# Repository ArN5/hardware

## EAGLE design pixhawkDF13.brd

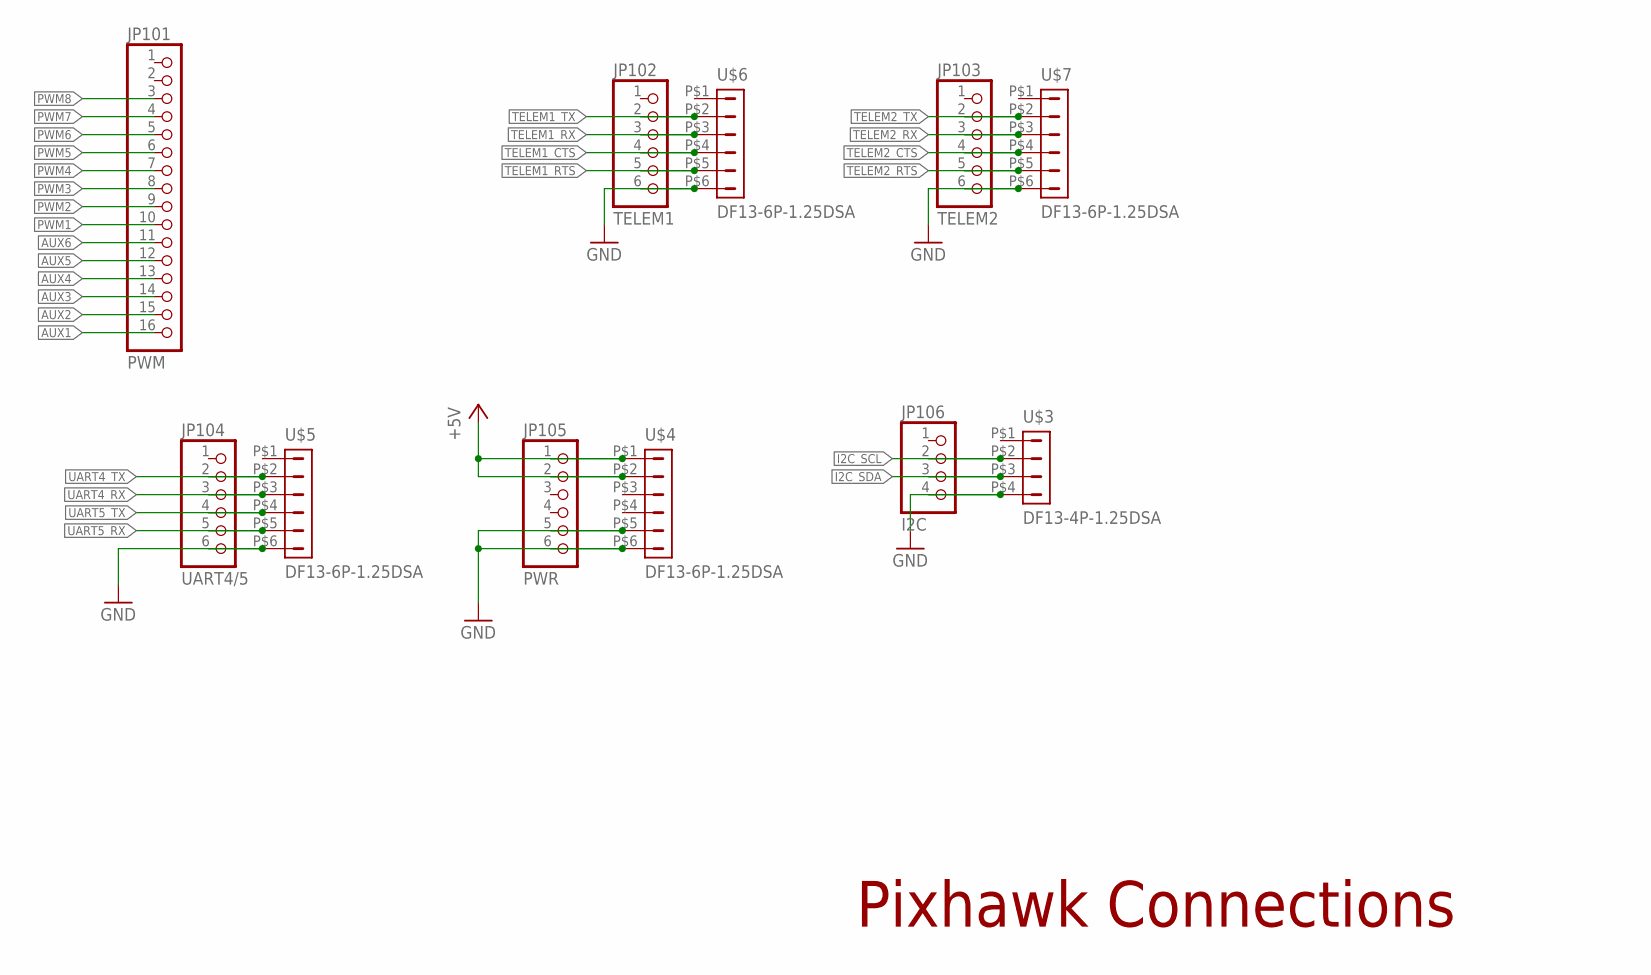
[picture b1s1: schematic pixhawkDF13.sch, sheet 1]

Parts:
JP101: PWM; 1X16
JP102: TELEM1; 1X06
JP103: TELEM2; 1X06
JP104: UART4/5; 1X06
JP105: PWR; 1X06
JP106: I2C; 1X04
U$3: DF13-4P-1.25DSA
U$4, U$5, U$6, U$7: DF13-6P-1.25DSA

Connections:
+5V: JP105.1, JP105.2, U$4.P$1 (1), U$4.P$2 (2); also elsewhere on the board
AUX1: JP101.16; also elsewhere on the board
AUX2: JP101.15; also elsewhere on the board
AUX3: JP101.14; also elsewhere on the board
AUX4: JP101.13; also elsewhere on the board
AUX5: JP101.12; also elsewhere on the board
AUX6: JP101.11; also elsewhere on the board
GND: JP102.6, JP103.6, JP104.6, JP105.5, JP105.6, JP106.4, U$3.P$4 (4), U$4.P$5 (5), U$4.P$6 (6), U$5.P$6 (6), U$6.P$6 (6), U$7.P$6 (6); also elsewhere on the board
I2C_SCL: JP106.2, U$3.P$2 (2); also elsewhere on the board
I2C_SDA: JP106.3, U$3.P$3 (3); also elsewhere on the board
PWM1: JP101.10; also elsewhere on the board
PWM2: JP101.9; also elsewhere on the board
PWM3: JP101.8; also elsewhere on the board
PWM4: JP101.7; also elsewhere on the board
PWM5: JP101.6; also elsewhere on the board
PWM6: JP101.5; also elsewhere on the board
PWM7: JP101.4; also elsewhere on the board
PWM8: JP101.3; also elsewhere on the board
TELEM1_CTS: JP102.4, U$6.P$4 (4)
TELEM1_RTS: JP102.5, U$6.P$5 (5)
TELEM1_RX: JP102.3, U$6.P$3 (3); also elsewhere on the board
TELEM1_TX: JP102.2, U$6.P$2 (2); also elsewhere on the board
TELEM2_CTS: JP103.4, U$7.P$4 (4)
TELEM2_RTS: JP103.5, U$7.P$5 (5)
TELEM2_RX: JP103.3, U$7.P$3 (3); also elsewhere on the board
TELEM2_TX: JP103.2, U$7.P$2 (2); also elsewhere on the board
UART4_RX: JP104.3, U$5.P$3 (3); also elsewhere on the board
UART4_TX: JP104.2, U$5.P$2 (2); also elsewhere on the board
UART5_RX: JP104.5, U$5.P$5 (5); also elsewhere on the board
UART5_TX: JP104.4, U$5.P$4 (4); also elsewhere on the board

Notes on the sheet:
Pixhawk Connections

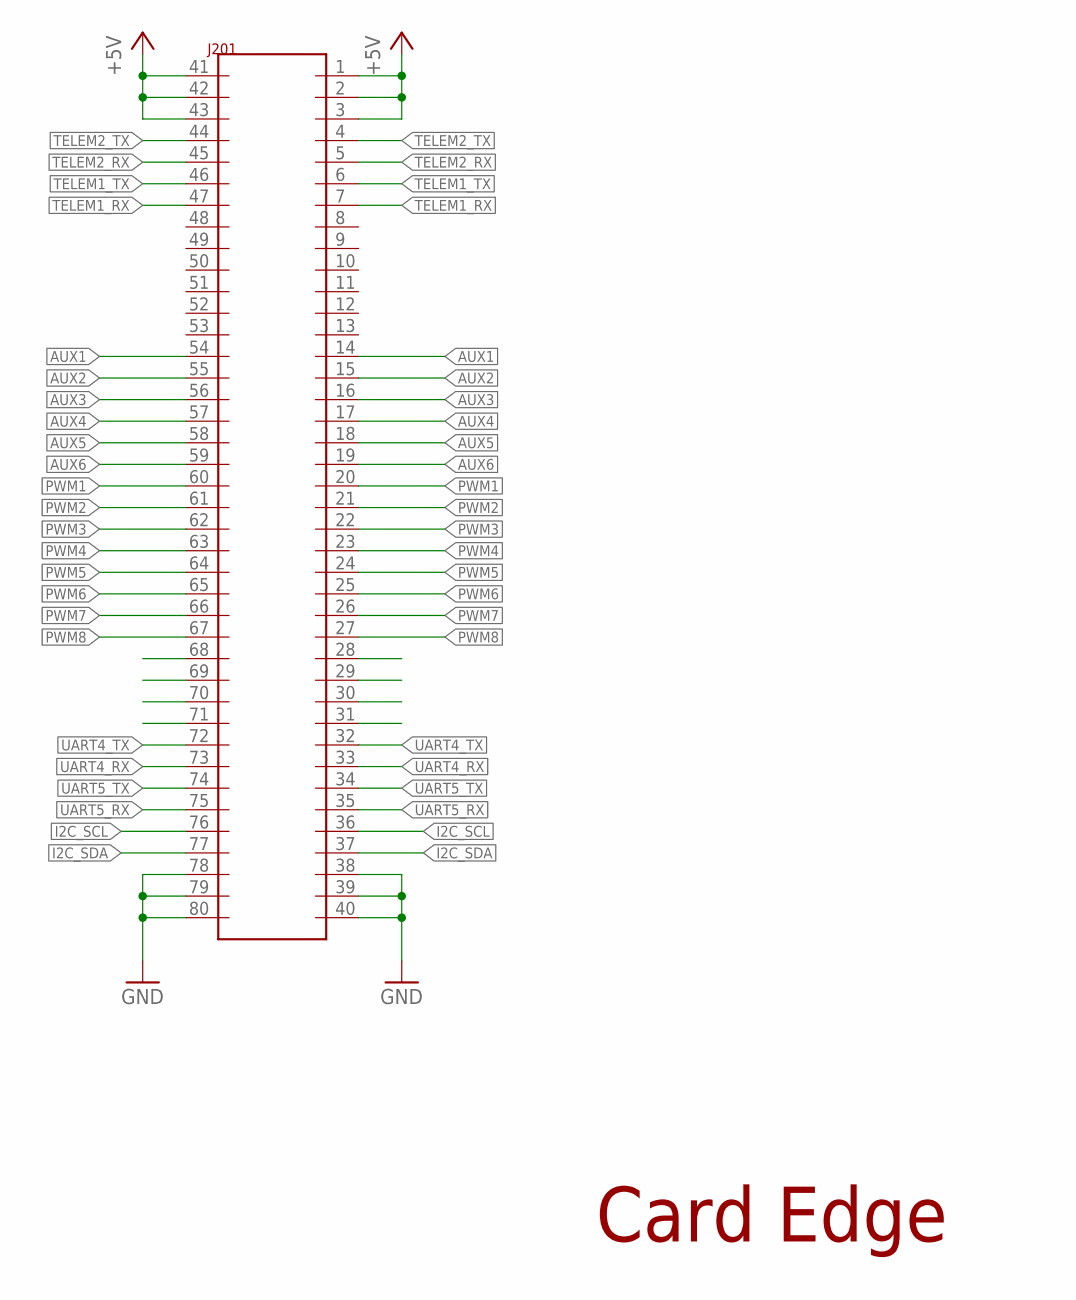
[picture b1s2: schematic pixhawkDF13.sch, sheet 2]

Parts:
J201: 80-PIN-CARD-EDGE

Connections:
+5V: J201.1, J201.2, J201.3, J201.41, J201.42, J201.43; also elsewhere on the board
AUX1: J201.14, J201.54; also elsewhere on the board
AUX2: J201.15, J201.55; also elsewhere on the board
AUX3: J201.16, J201.56; also elsewhere on the board
AUX4: J201.17, J201.57; also elsewhere on the board
AUX5: J201.18, J201.58; also elsewhere on the board
AUX6: J201.19, J201.59; also elsewhere on the board
CAN_H: J201.30, J201.70
CAN_L: J201.31, J201.71
GND: J201.38, J201.39, J201.40, J201.78, J201.79, J201.80; also elsewhere on the board
I2C_SCL: J201.36, J201.76; also elsewhere on the board
I2C_SDA: J201.37, J201.77; also elsewhere on the board
PWM1: J201.20, J201.60; also elsewhere on the board
PWM2: J201.21, J201.61; also elsewhere on the board
PWM3: J201.22, J201.62; also elsewhere on the board
PWM4: J201.23, J201.63; also elsewhere on the board
PWM5: J201.24, J201.64; also elsewhere on the board
PWM6: J201.25, J201.65; also elsewhere on the board
PWM7: J201.26, J201.66; also elsewhere on the board
PWM8: J201.27, J201.67; also elsewhere on the board
TELEM1_RX: J201.7, J201.47; also elsewhere on the board
TELEM1_TX: J201.6, J201.46; also elsewhere on the board
TELEM2_RX: J201.5, J201.45; also elsewhere on the board
TELEM2_TX: J201.4, J201.44; also elsewhere on the board
UART4_RX: J201.33, J201.73; also elsewhere on the board
UART4_TX: J201.32, J201.72; also elsewhere on the board
UART5_RX: J201.35, J201.75; also elsewhere on the board
UART5_TX: J201.34, J201.74; also elsewhere on the board

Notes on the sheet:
Card Edge

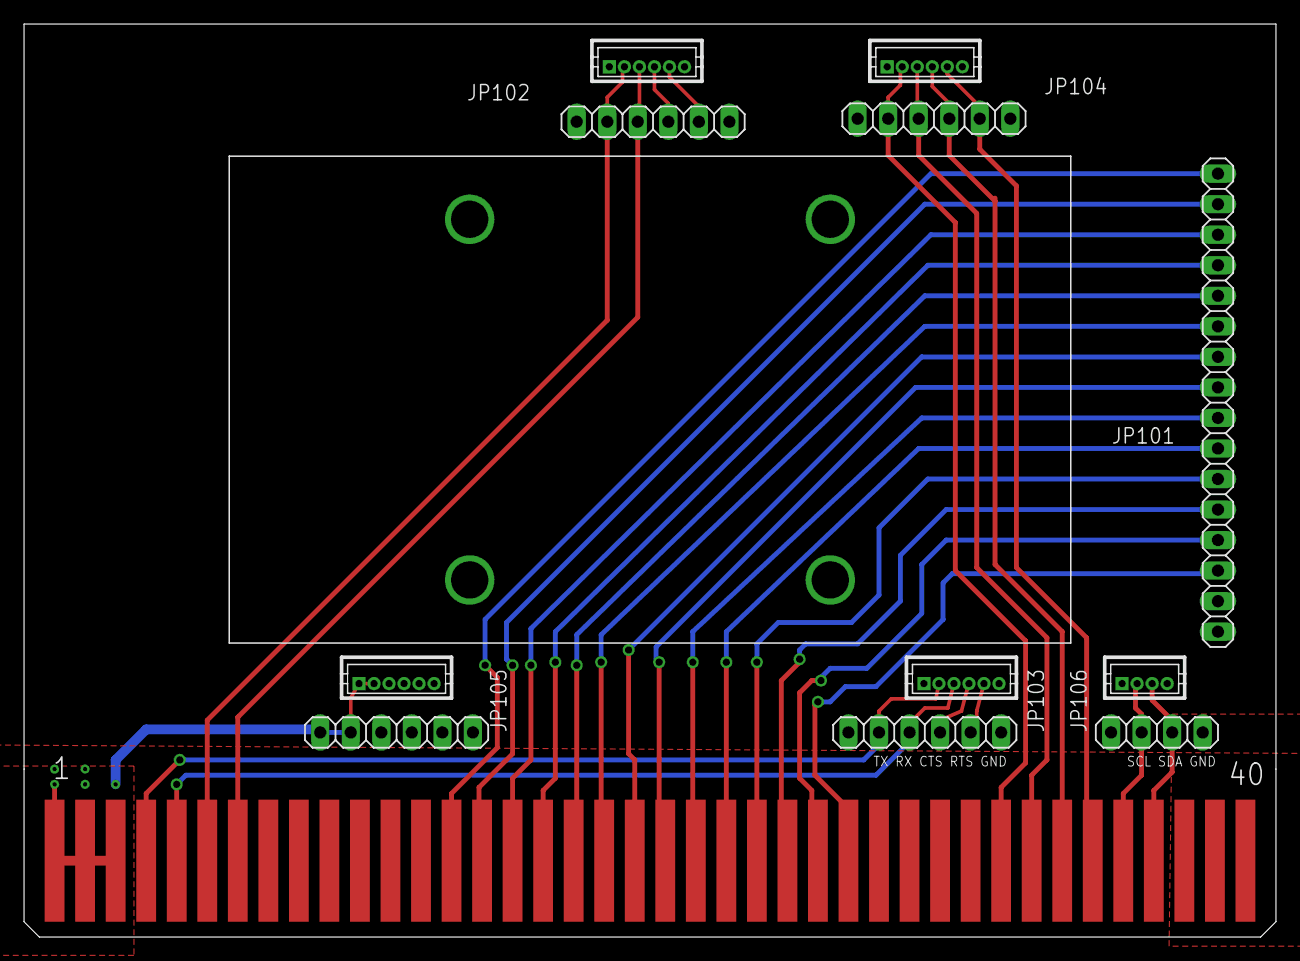
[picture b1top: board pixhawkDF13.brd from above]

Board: 2 copper layers, 104.1 x 75.9 mm, 14 parts (1 on the bottom side), 32 nets.

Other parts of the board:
U$1: PIXHAWK_MOUNTING_HOLES
U$2: ILLINOISAUV

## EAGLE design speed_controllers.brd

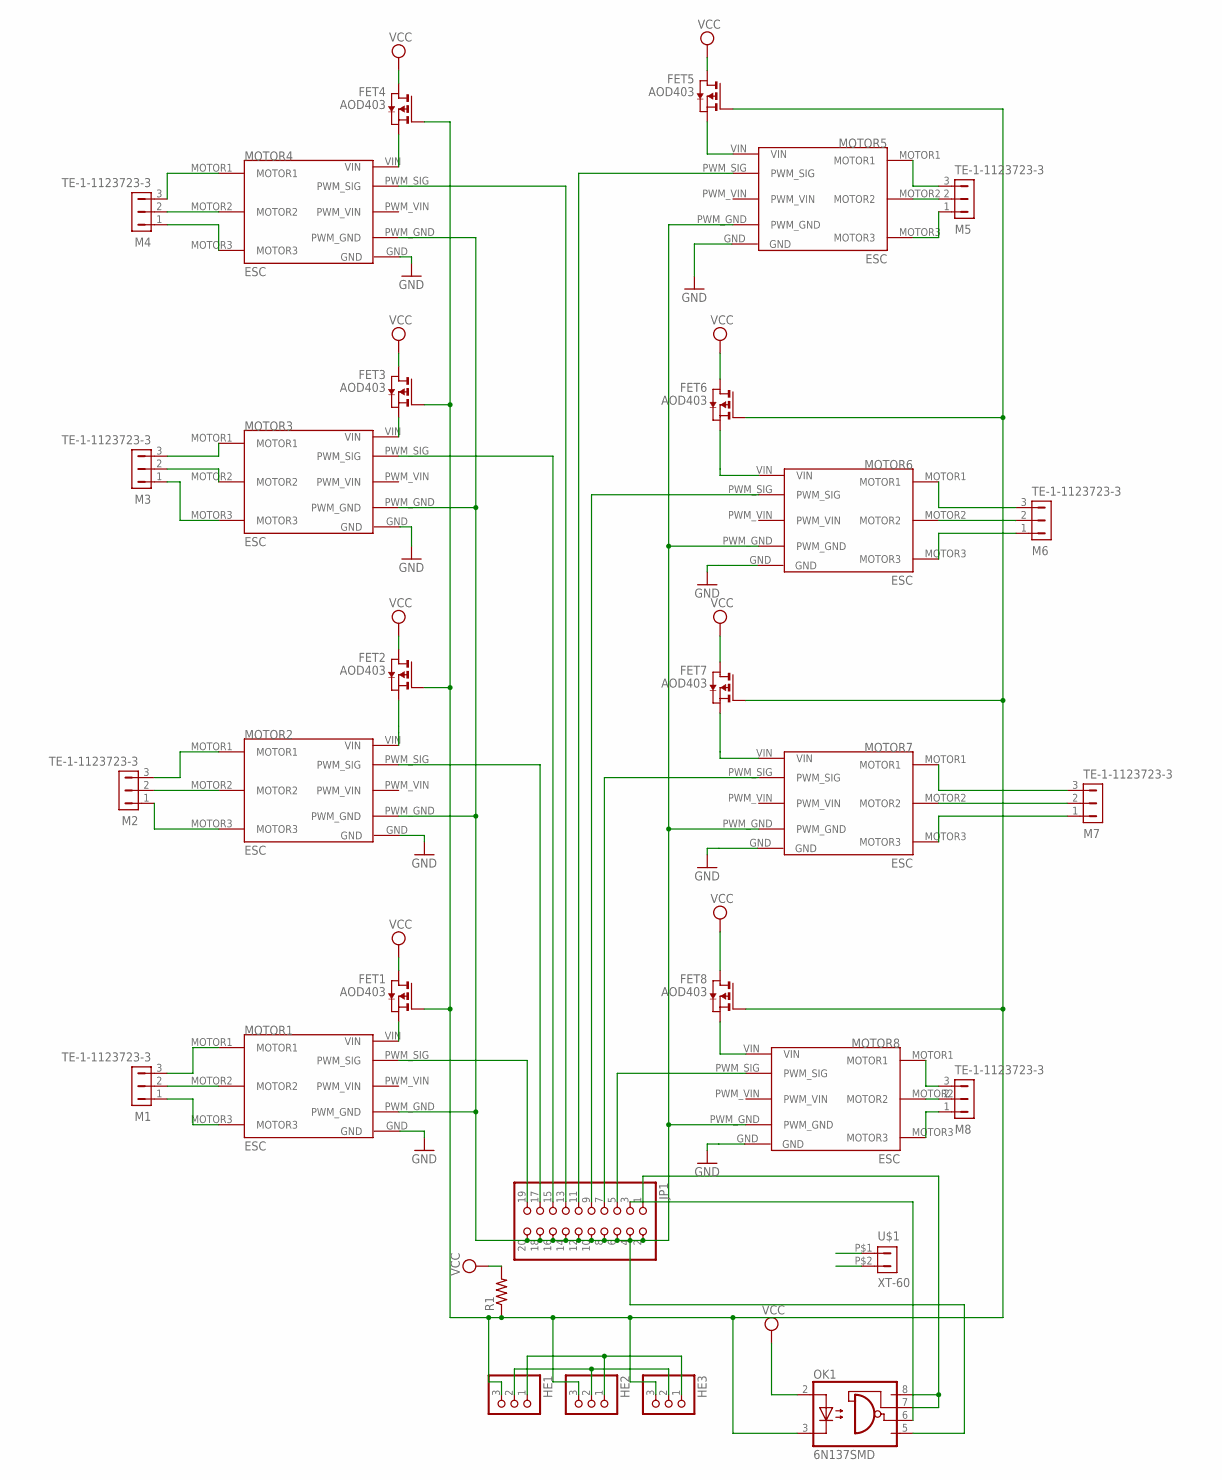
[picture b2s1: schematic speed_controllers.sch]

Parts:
FET1, FET2, FET3, FET4, FET5, FET6, FET7, FET8: AOD403; TO252
HE1, HE2, HE3: PINHD-1X3; 1X03
JP1: PINHD-2X10; 2X10
M1, M2, M3, M4, M5, M6, M7, M8: TE-1-1123723-3
MOTOR1, MOTOR2, MOTOR3, MOTOR4, MOTOR5, MOTOR6, MOTOR7, MOTOR8: ESC
OK1: 6N137SMD; DIL8-SMD
R1: R-US_R0603; R0603
U$1: XT-60

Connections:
FET_G: FET1.G, FET2.G, FET3.G, FET4.G, FET5.G, FET6.G, FET7.G, FET8.G, HE1.3, HE2.3, HE3.3, OK1.3 (C), R1.1
GND: HE1.2, HE2.2, HE3.2, MOTOR1.GND, MOTOR2.GND, MOTOR3.GND, MOTOR4.GND, MOTOR5.GND, MOTOR6.GND, MOTOR7.GND, MOTOR8.GND, U$1.P$2 (2)
M1_1: M1.1, MOTOR1.MOTOR3
M1_2: M1.2, MOTOR1.MOTOR2
M1_3: M1.3, MOTOR1.MOTOR1
M2_1: M2.1, MOTOR2.MOTOR3
M2_2: M2.2, MOTOR2.MOTOR2
M2_3: M2.3, MOTOR2.MOTOR1
M3_1: M3.1, MOTOR3.MOTOR3
M3_2: M3.2, MOTOR3.MOTOR2
M3_3: M3.3, MOTOR3.MOTOR1
M4_1: M4.1, MOTOR4.MOTOR3
M4_2: M4.2, MOTOR4.MOTOR2
M4_3: M4.3, MOTOR4.MOTOR1
M5_1: M5.1, MOTOR5.MOTOR3
M5_2: M5.2, MOTOR5.MOTOR2
M5_3: M5.3, MOTOR5.MOTOR1
M6_1: M6.1, MOTOR6.MOTOR3
M6_2: M6.2, MOTOR6.MOTOR2
M6_3: M6.3, MOTOR6.MOTOR1
M7_1: M7.1, MOTOR7.MOTOR3
M7_2: M7.2, MOTOR7.MOTOR2
M7_3: M7.3, MOTOR7.MOTOR1
M8_1: M8.1, MOTOR8.MOTOR3
M8_2: M8.2, MOTOR8.MOTOR2
M8_3: M8.3, MOTOR8.MOTOR1
unnamed: JP1.1, OK1.7 (VE), OK1.8 (VCC)
unnamed: JP1.3, OK1.6 (VO)
PWM_GND: JP1.2, JP1.4, JP1.6, JP1.8, JP1.10, JP1.12, JP1.14, JP1.16, JP1.18, JP1.20, MOTOR1.PWM_GND, MOTOR2.PWM_GND, MOTOR3.PWM_GND, MOTOR4.PWM_GND, MOTOR5.PWM_GND, MOTOR6.PWM_GND, MOTOR7.PWM_GND, MOTOR8.PWM_GND, OK1.5 (GND)
SIG_1: JP1.19, MOTOR1.PWM_SIG
SIG_2: JP1.17, MOTOR2.PWM_SIG
SIG_3: JP1.15, MOTOR3.PWM_SIG
SIG_4: JP1.13, MOTOR4.PWM_SIG
SIG_5: JP1.11, MOTOR5.PWM_SIG
SIG_6: JP1.9, MOTOR6.PWM_SIG
SIG_7: JP1.7, MOTOR7.PWM_SIG
SIG_8: JP1.5, MOTOR8.PWM_SIG
VCC: FET1.D, FET2.D, FET3.D, FET4.D, FET5.D, FET6.D, FET7.D, FET8.D, HE1.1, HE2.1, HE3.1, OK1.2 (A), R1.2, U$1.P$1 (1)
VIN3: FET3.S, MOTOR3.VIN
VIN_1: FET1.S, MOTOR1.VIN
VIN_2: FET2.S, MOTOR2.VIN
VIN_4: FET4.S, MOTOR4.VIN
VIN_5: FET5.S, MOTOR5.VIN
VIN_6: FET6.S, MOTOR6.VIN
VIN_7: FET7.S, MOTOR7.VIN
VIN_8: FET8.S, MOTOR8.VIN

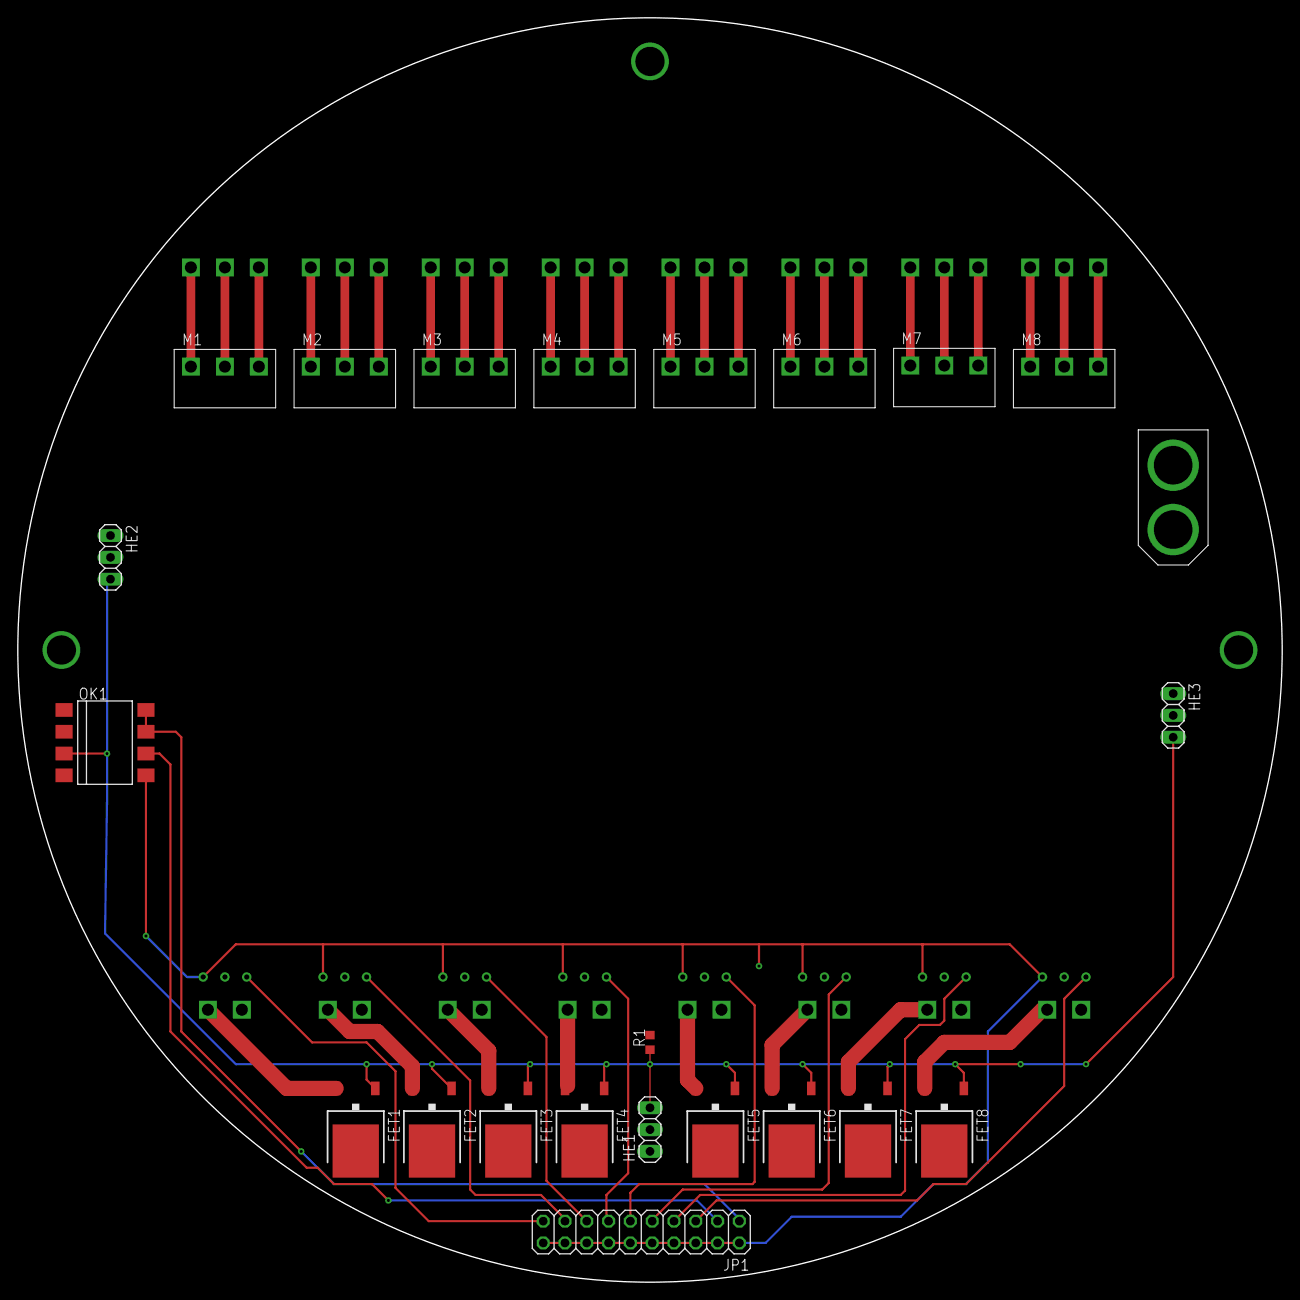
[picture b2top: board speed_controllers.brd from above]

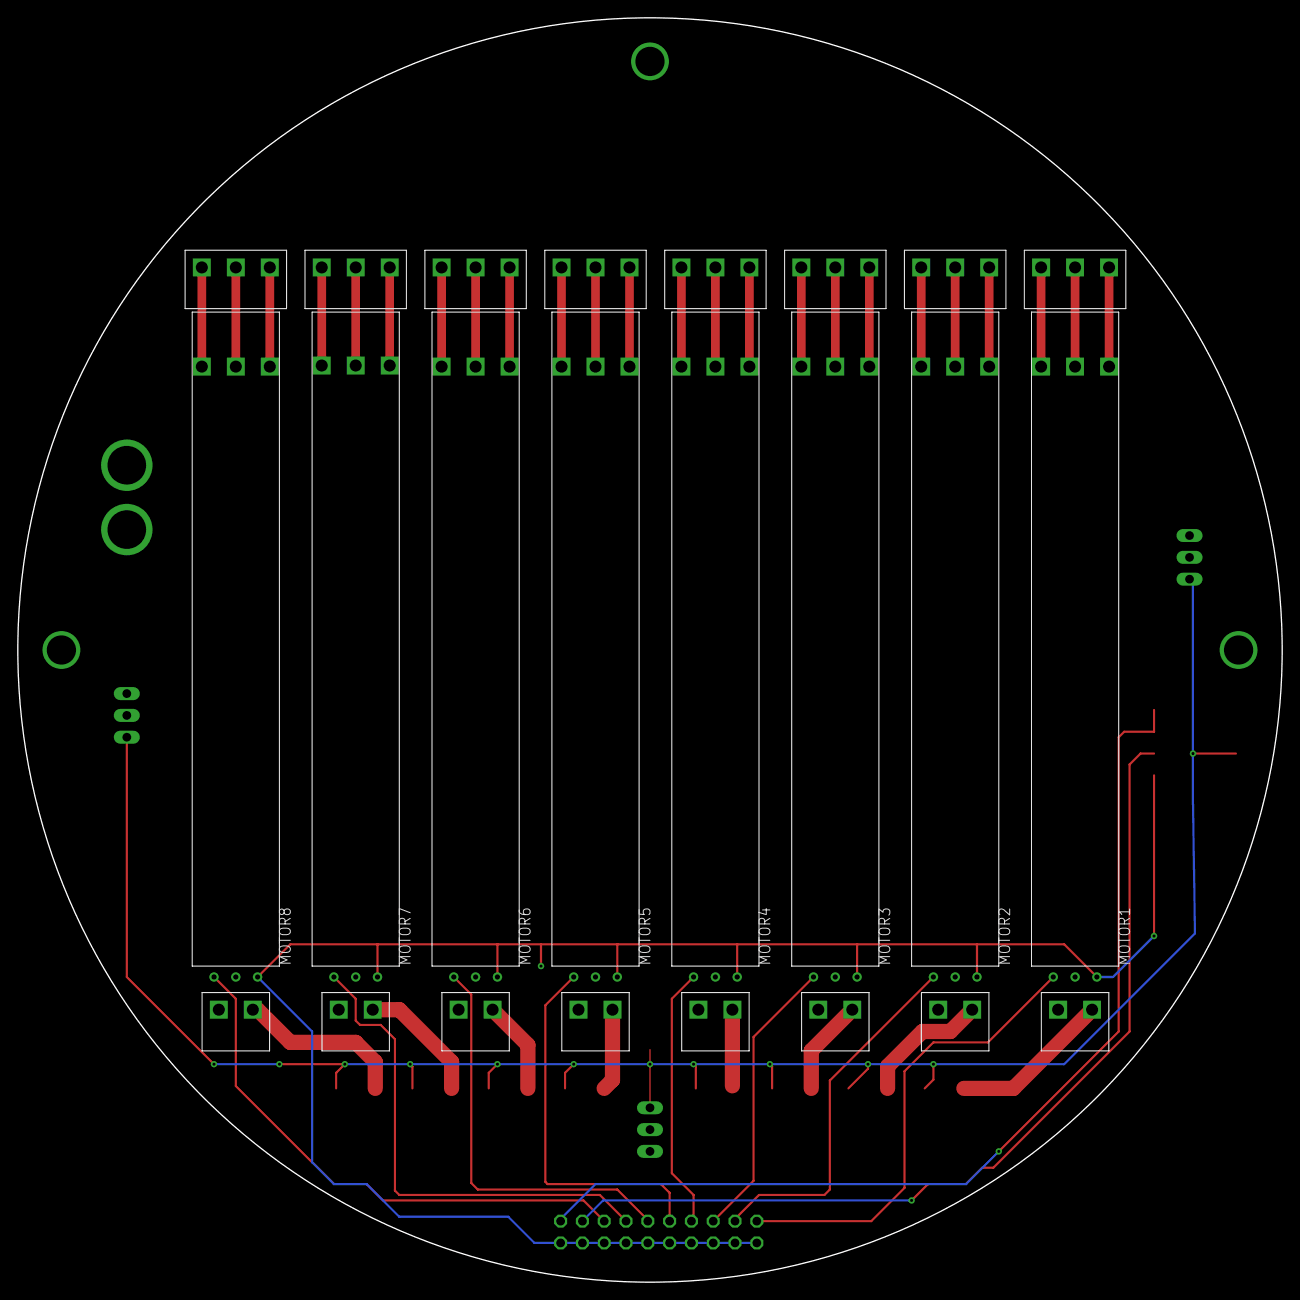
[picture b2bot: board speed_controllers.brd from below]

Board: 2 copper layers, 147.3 x 147.3 mm, 31 parts (8 on the bottom side), 46 nets.

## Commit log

2018-02-12 Redone ESC boards
2018-02-18 Fixed everything in issue Redone ESC boards #2
2018-02-25 Added Optocoupler and Hall effect sensors
2018-02-26 Rewired optocontroller
2018-03-01 Changed optocoupler to SMD
2018-03-31 added the DF13 connectors and made the board compact. the file is pixhawkDF13.Those connectors are very tiny so im getting spacing errors from eagle. Remove them if they are too much of an issue.
2018-03-31 DF13 connectors
    eagle library containing the DF13 connectors https://github.com/chiengineer/Eagle-Libraries/blob/master/Connectors/con-hirose-df13.lbr
